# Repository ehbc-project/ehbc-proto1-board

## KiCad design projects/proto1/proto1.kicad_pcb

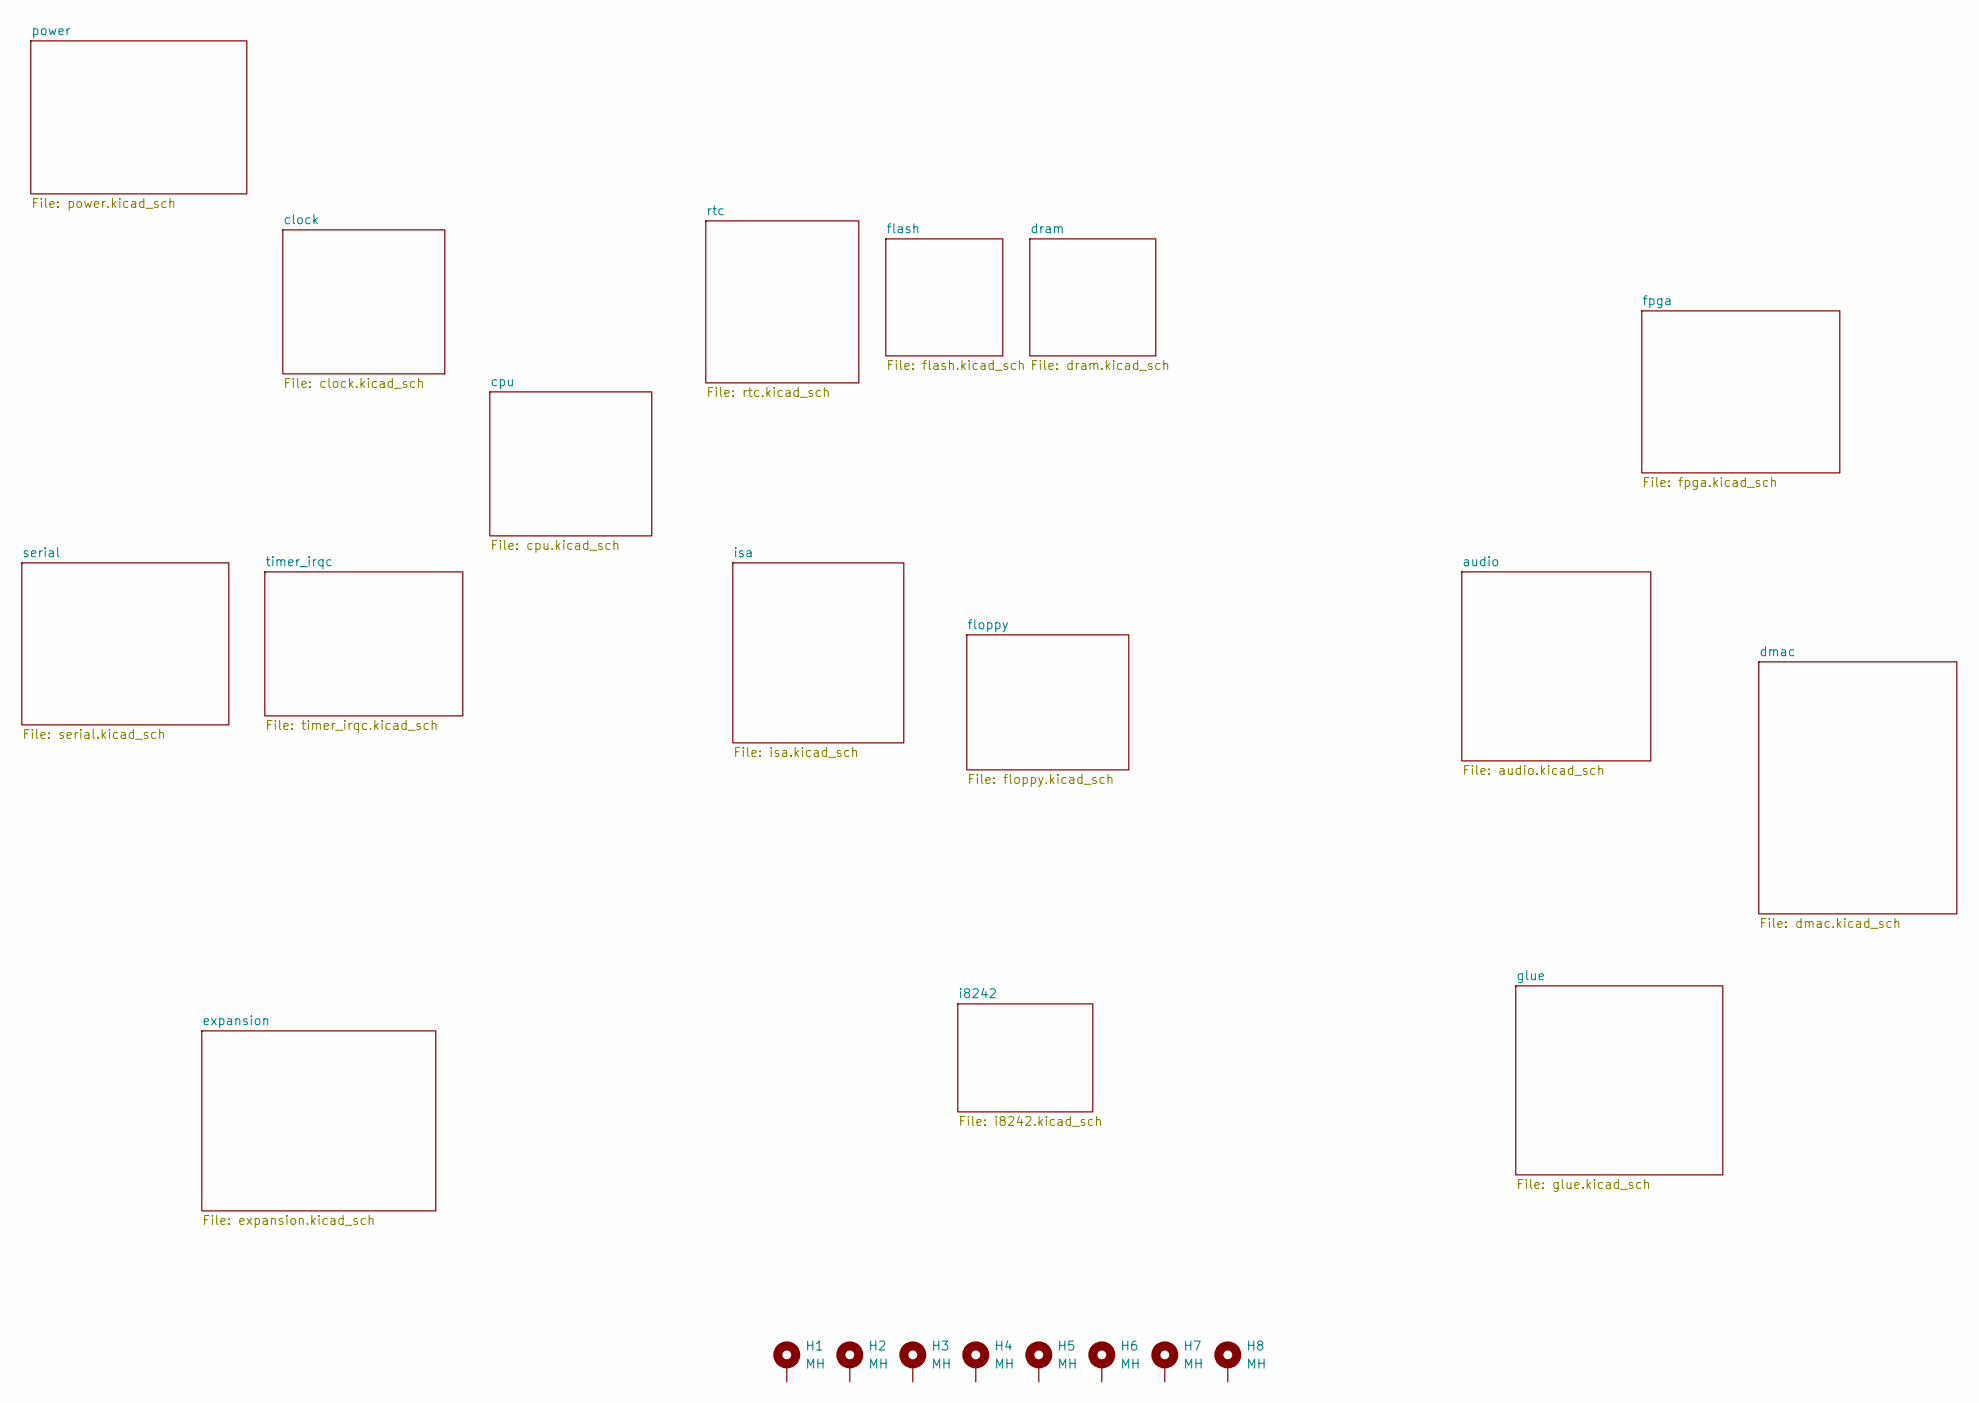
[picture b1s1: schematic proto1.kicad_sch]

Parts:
H1, H2, H3, H4, H5, H6, H7, H8: MH; MountingHole_3.2mm_M3_Pad

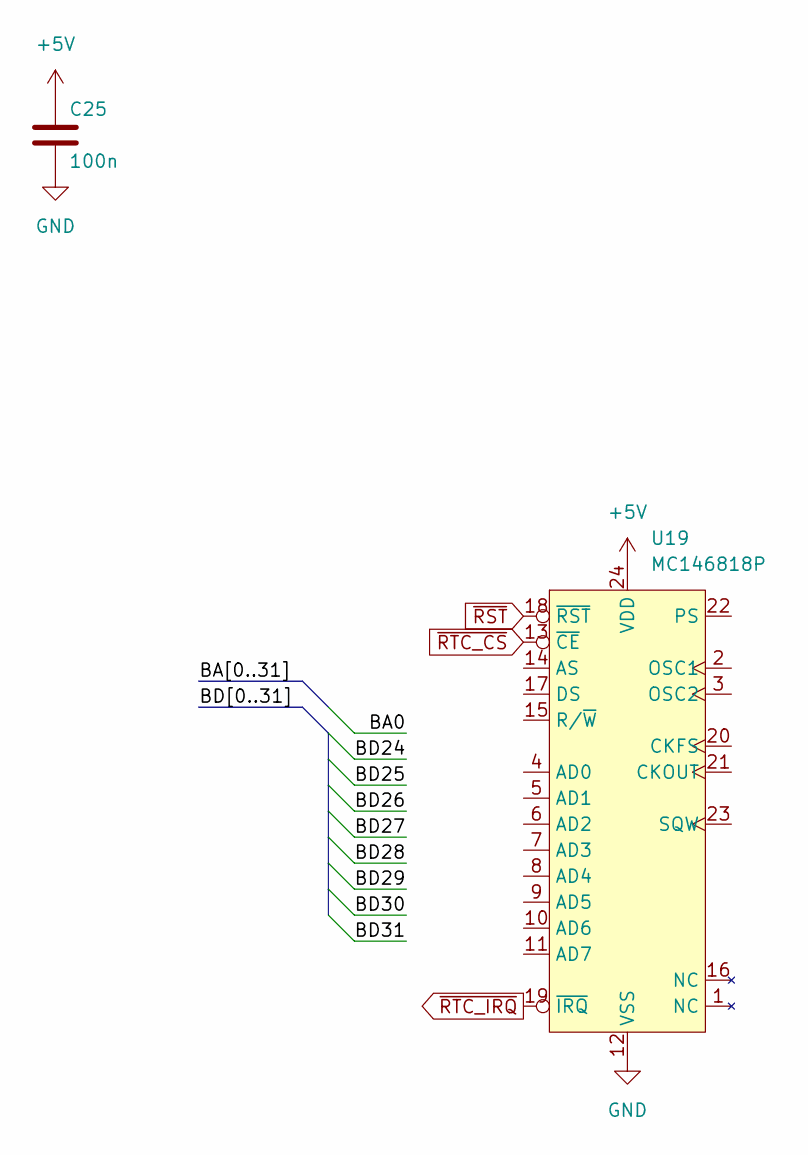
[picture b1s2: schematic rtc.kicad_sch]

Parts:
C25: 100n; C_Disc_D4.3mm_W1.9mm_P5.00mm
U19: MC146818P; DIP-24_W10.16mm

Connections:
+5V: C25.1, U19.24 (VDD); also elsewhere on the board
GND: C25.2, U19.12 (VSS); also elsewhere on the board
~RST: U19.18 (~RST); also elsewhere on the board
~RTC_CS: U19.13 (~CE)
~RTC_IRQ: U19.19 (~IRQ); also elsewhere on the board

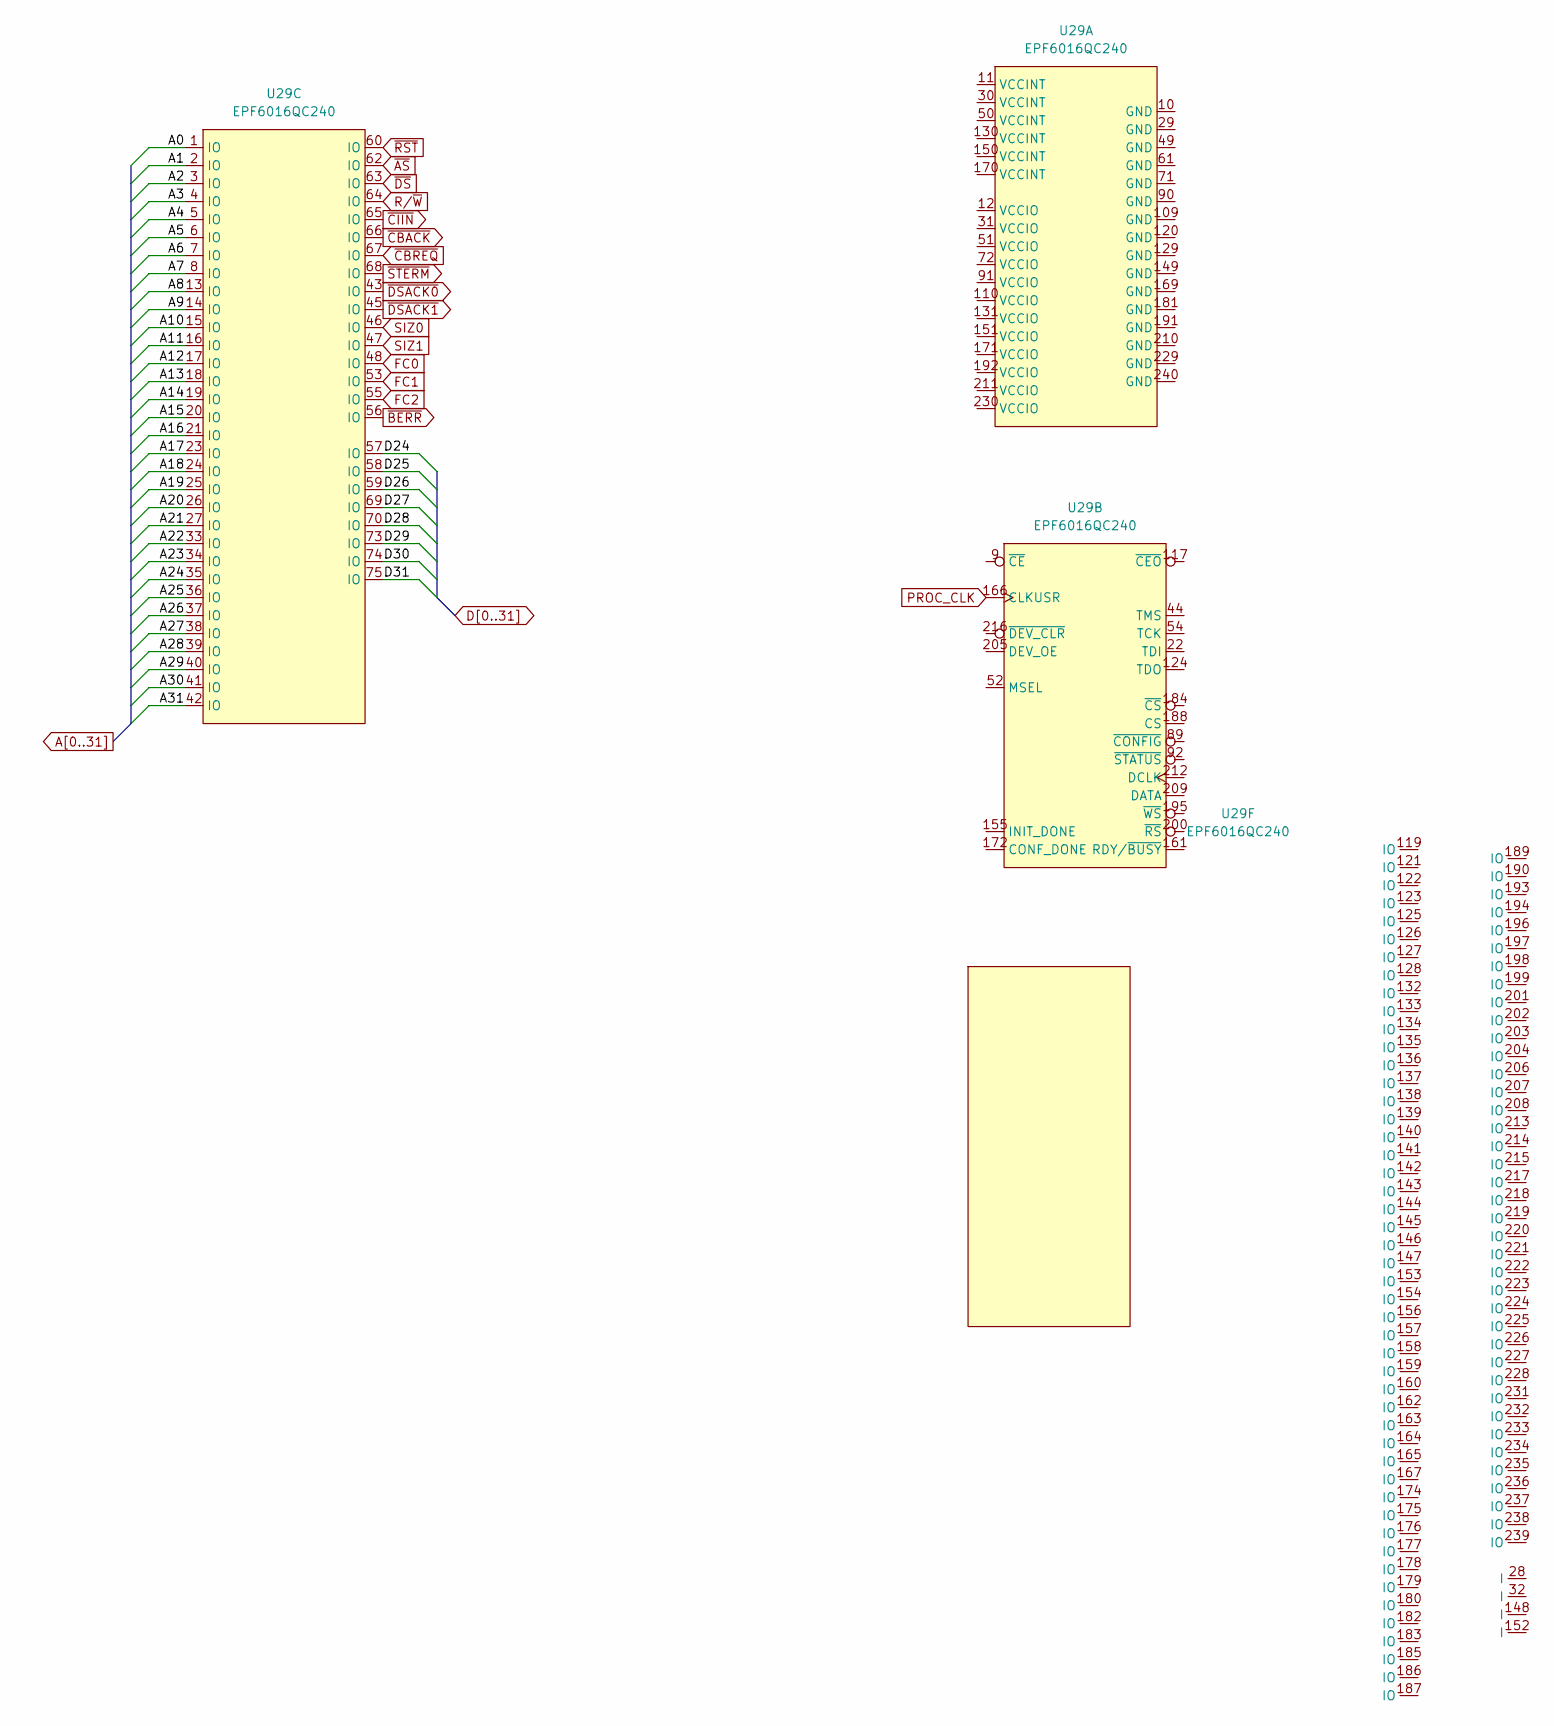
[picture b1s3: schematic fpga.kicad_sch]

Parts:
U29: EPF6016QC240; PQFP-240_32.1x32.1mm_P0.5mm

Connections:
A0: U29.1 (IO); also elsewhere on the board
A1: U29.2 (IO); also elsewhere on the board
A2: U29.3 (IO); also elsewhere on the board
A3: U29.4 (IO); also elsewhere on the board
A4: U29.5 (IO); also elsewhere on the board
A5: U29.6 (IO); also elsewhere on the board
A6: U29.7 (IO); also elsewhere on the board
A7: U29.8 (IO); also elsewhere on the board
A8: U29.13 (IO); also elsewhere on the board
A9: U29.14 (IO); also elsewhere on the board
A10: U29.15 (IO); also elsewhere on the board
A11: U29.16 (IO); also elsewhere on the board
A12: U29.17 (IO); also elsewhere on the board
A13: U29.18 (IO); also elsewhere on the board
A14: U29.19 (IO); also elsewhere on the board
A15: U29.20 (IO); also elsewhere on the board
A16: U29.21 (IO); also elsewhere on the board
A17: U29.23 (IO); also elsewhere on the board
A18: U29.24 (IO); also elsewhere on the board
A19: U29.25 (IO); also elsewhere on the board
A20: U29.26 (IO); also elsewhere on the board
A21: U29.27 (IO); also elsewhere on the board
A22: U29.33 (IO); also elsewhere on the board
A23: U29.34 (IO); also elsewhere on the board
A24: U29.35 (IO); also elsewhere on the board
A25: U29.36 (IO); also elsewhere on the board
A26: U29.37 (IO); also elsewhere on the board
A27: U29.38 (IO); also elsewhere on the board
A28: U29.39 (IO); also elsewhere on the board
A29: U29.40 (IO); also elsewhere on the board
A30: U29.41 (IO); also elsewhere on the board
A31: U29.42 (IO); also elsewhere on the board
D24: U29.57 (IO); also elsewhere on the board
D25: U29.58 (IO); also elsewhere on the board
D26: U29.59 (IO); also elsewhere on the board
D27: U29.69 (IO); also elsewhere on the board
D28: U29.70 (IO); also elsewhere on the board
D29: U29.73 (IO); also elsewhere on the board
D30: U29.74 (IO); also elsewhere on the board
D31: U29.75 (IO); also elsewhere on the board
FC0: U29.48 (IO); also elsewhere on the board
FC1: U29.53 (IO); also elsewhere on the board
FC2: U29.55 (IO); also elsewhere on the board
PROC_CLK: U29.166 (CLKUSR); also elsewhere on the board
R/~W: U29.64 (IO); also elsewhere on the board
SIZ0: U29.46 (IO); also elsewhere on the board
SIZ1: U29.47 (IO); also elsewhere on the board
~AS: U29.62 (IO); also elsewhere on the board
~BERR: U29.56 (IO); also elsewhere on the board
~CBACK: U29.66 (IO); also elsewhere on the board
~CBREQ: U29.67 (IO); also elsewhere on the board
~CIIN: U29.65 (IO); also elsewhere on the board
~DSACK0: U29.43 (IO); also elsewhere on the board
~DSACK1: U29.45 (IO); also elsewhere on the board
~DS: U29.63 (IO); also elsewhere on the board
~RST: U29.60 (IO); also elsewhere on the board
~STERM: U29.68 (IO); also elsewhere on the board

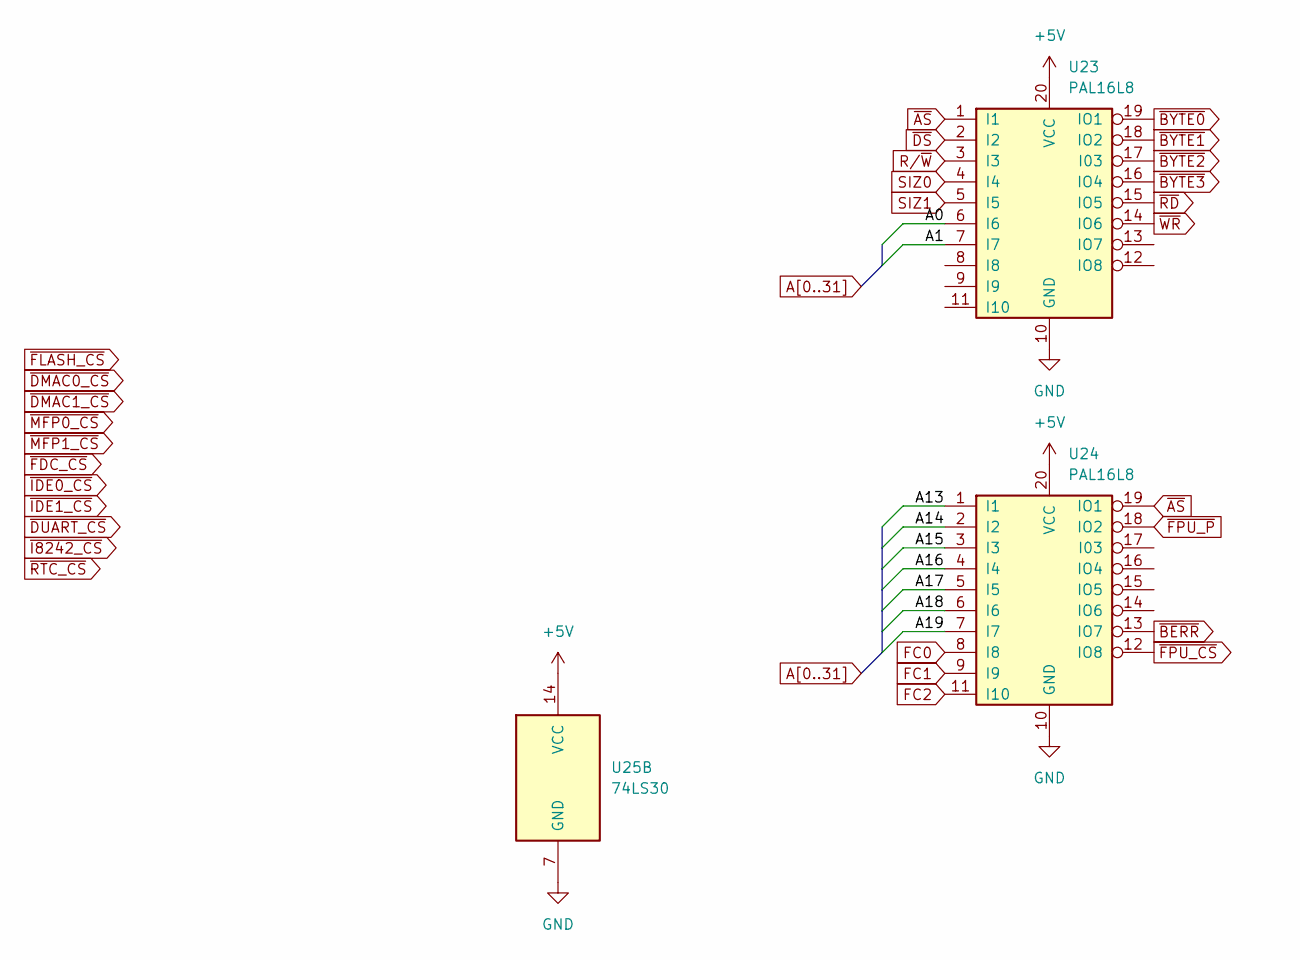
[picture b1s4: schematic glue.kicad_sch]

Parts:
U23, U24: PAL16L8; DIP-20_W7.62mm_Socket
U25: 74LS30

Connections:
+5V: U23.20 (VCC), U24.20 (VCC), U25.14 (VCC); also elsewhere on the board
A0: U23.6 (I6); also elsewhere on the board
A1: U23.7 (I7); also elsewhere on the board
A13: U24.1 (I1); also elsewhere on the board
A14: U24.2 (I2); also elsewhere on the board
A15: U24.3 (I3); also elsewhere on the board
A16: U24.4 (I4); also elsewhere on the board
A17: U24.5 (I5); also elsewhere on the board
A18: U24.6 (I6); also elsewhere on the board
A19: U24.7 (I7); also elsewhere on the board
FC0: U24.8 (I8); also elsewhere on the board
FC1: U24.9 (I9); also elsewhere on the board
FC2: U24.11 (I10); also elsewhere on the board
GND: U23.10 (GND), U24.10 (GND), U25.7 (GND); also elsewhere on the board
R/~W: U23.3 (I3); also elsewhere on the board
SIZ0: U23.4 (I4); also elsewhere on the board
SIZ1: U23.5 (I5); also elsewhere on the board
~AS: U23.1 (I1), U24.19 (IO1); also elsewhere on the board
~BERR: U24.13 (IO7); also elsewhere on the board
~BYTE0: U23.19 (IO1)
~BYTE1: U23.18 (IO2)
~BYTE2: U23.17 (I03)
~BYTE3: U23.16 (IO4)
~DS: U23.2 (I2); also elsewhere on the board
~FPU_CS: U24.12 (IO8); also elsewhere on the board
~FPU_P: U24.18 (IO2); also elsewhere on the board
~RD: U23.15 (IO5); also elsewhere on the board
~WR: U23.14 (IO6); also elsewhere on the board

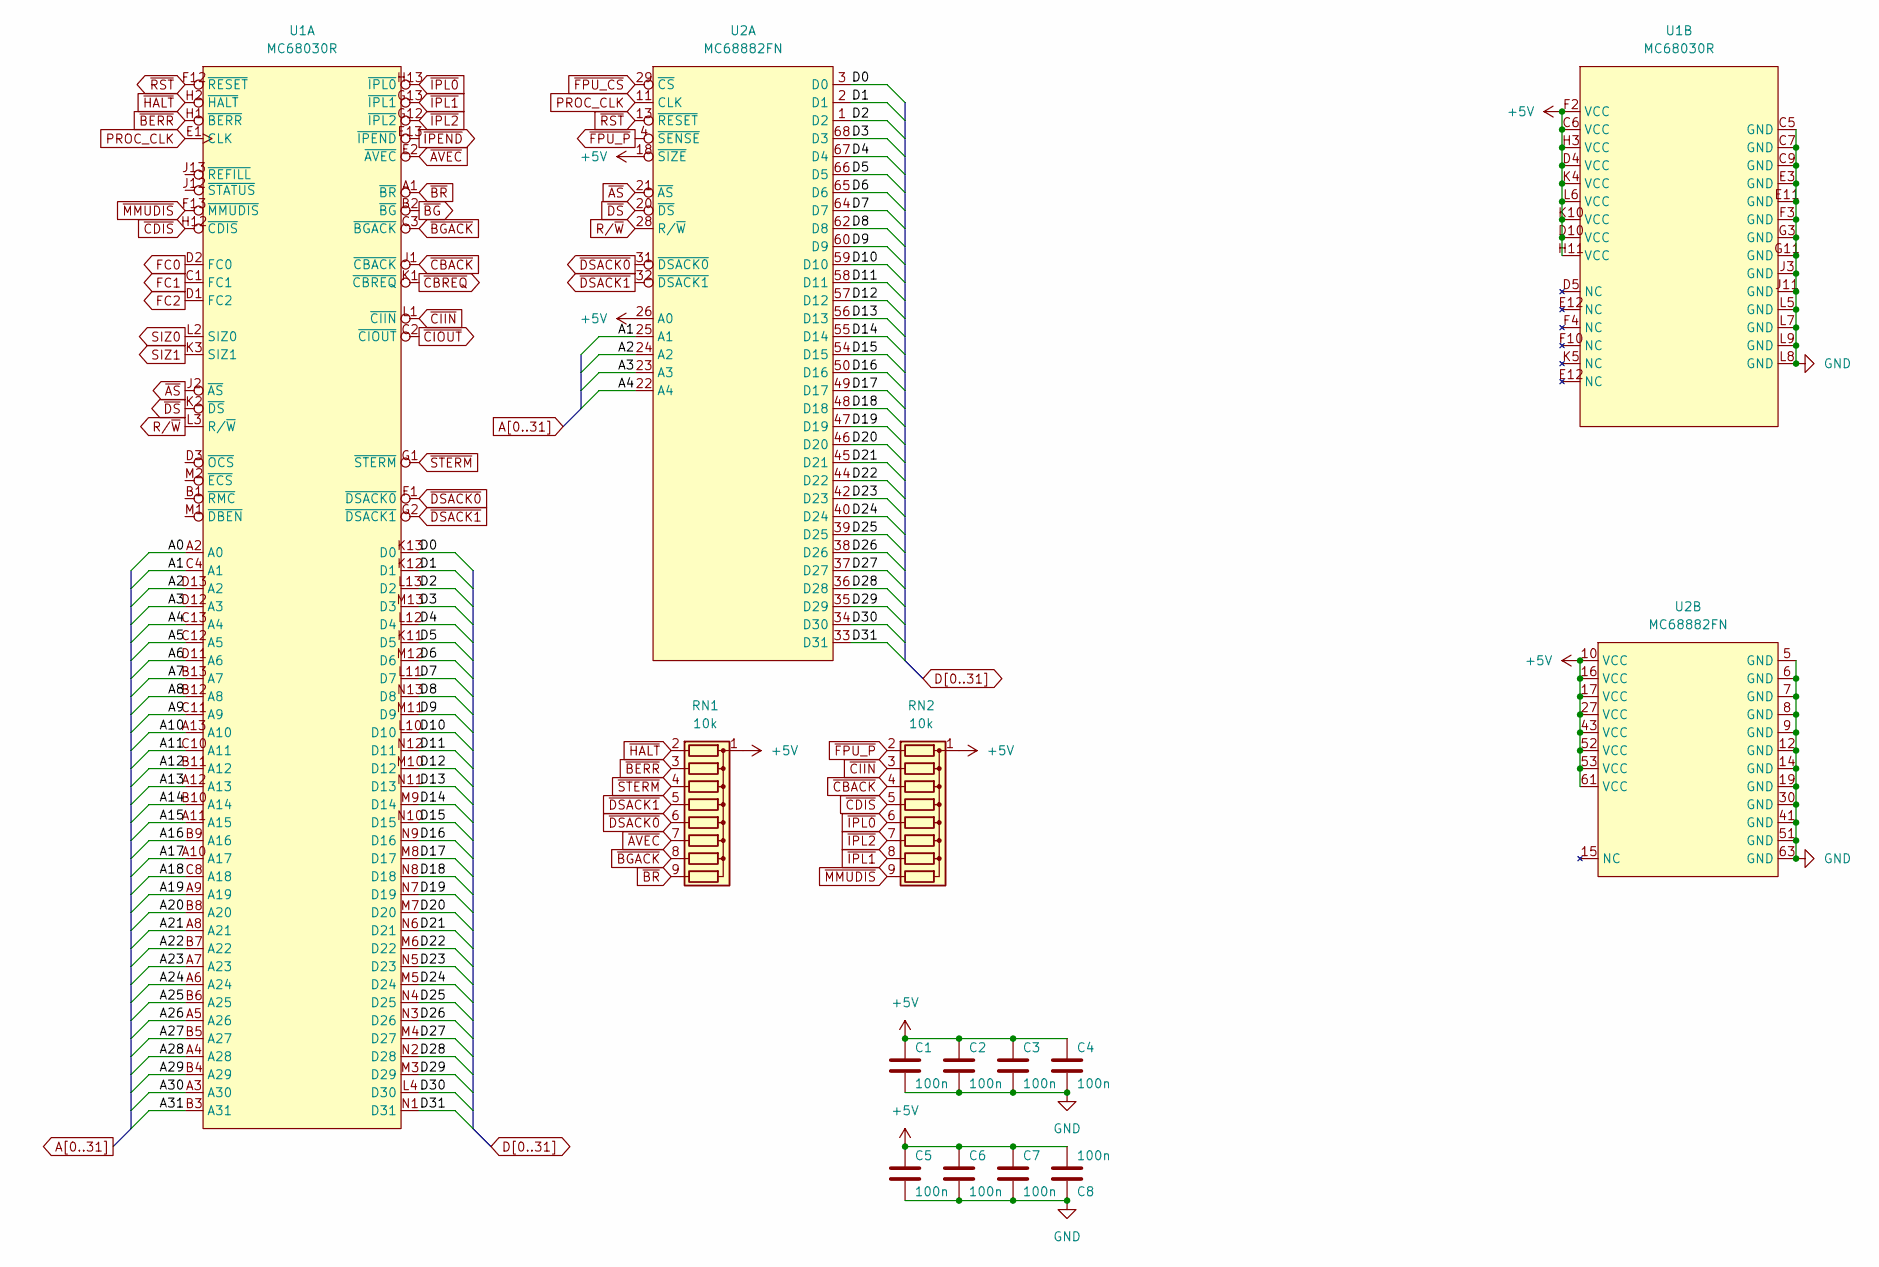
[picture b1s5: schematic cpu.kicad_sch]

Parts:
C1, C2, C3, C4, C5, C6, C7, C8: 100n; C_Disc_D4.3mm_W1.9mm_P5.00mm
RN1, RN2: 10k; R_Array_SIP9
U1: MC68030R; PGA128
U2: MC68882FN; PLCC-68_THT-Socket

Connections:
+5V: C1.1, C2.1, C3.1, C4.1, C5.1, C6.1, C7.1, C8.2, RN1.1 (common), RN2.1 (common), U1.C6 (VCC), U1.D4 (VCC), U1.D10 (VCC), U1.F2 (VCC), U1.H3 (VCC), U1.H11 (VCC), U1.K4 (VCC), U1.K10 (VCC), U1.L6 (VCC), U2.10 (VCC), U2.16 (VCC), U2.17 (VCC), U2.18 (~SIZE), U2.26 (A0), U2.27 (VCC), U2.43 (VCC), U2.52 (VCC), U2.53 (VCC), U2.61 (VCC); also elsewhere on the board
A0: U1.A2 (A0); also elsewhere on the board
A1: U1.C4 (A1), U2.25 (A1); also elsewhere on the board
A2: U1.D13 (A2), U2.24 (A2); also elsewhere on the board
A3: U1.D12 (A3), U2.23 (A3); also elsewhere on the board
A4: U1.C13 (A4), U2.22 (A4); also elsewhere on the board
A5: U1.C12 (A5); also elsewhere on the board
A6: U1.D11 (A6); also elsewhere on the board
A7: U1.B13 (A7); also elsewhere on the board
A8: U1.B12 (A8); also elsewhere on the board
A9: U1.C11 (A9); also elsewhere on the board
A10: U1.A13 (A10); also elsewhere on the board
A11: U1.C10 (A11); also elsewhere on the board
A12: U1.B11 (A12); also elsewhere on the board
A13: U1.A12 (A13); also elsewhere on the board
A14: U1.B10 (A14); also elsewhere on the board
A15: U1.A11 (A15); also elsewhere on the board
A16: U1.B9 (A16); also elsewhere on the board
A17: U1.A10 (A17); also elsewhere on the board
A18: U1.C8 (A18); also elsewhere on the board
A19: U1.A9 (A19); also elsewhere on the board
A20: U1.B8 (A20); also elsewhere on the board
A21: U1.A8 (A21); also elsewhere on the board
A22: U1.B7 (A22); also elsewhere on the board
A23: U1.A7 (A23); also elsewhere on the board
A24: U1.A6 (A24); also elsewhere on the board
A25: U1.B6 (A25); also elsewhere on the board
A26: U1.A5 (A26); also elsewhere on the board
A27: U1.B5 (A27); also elsewhere on the board
A28: U1.A4 (A28); also elsewhere on the board
A29: U1.B4 (A29); also elsewhere on the board
A30: U1.A3 (A30); also elsewhere on the board
A31: U1.B3 (A31); also elsewhere on the board
D0: U1.K13 (D0), U2.3 (D0); also elsewhere on the board
D1: U1.K12 (D1), U2.2 (D1); also elsewhere on the board
D2: U1.L13 (D2), U2.1 (D2); also elsewhere on the board
D3: U1.M13 (D3), U2.68 (D3); also elsewhere on the board
D4: U1.L12 (D4), U2.67 (D4); also elsewhere on the board
D5: U1.K11 (D5), U2.66 (D5); also elsewhere on the board
D6: U1.M12 (D6), U2.65 (D6); also elsewhere on the board
D7: U1.L11 (D7), U2.64 (D7); also elsewhere on the board
D8: U1.N13 (D8), U2.62 (D8); also elsewhere on the board
D9: U1.M11 (D9), U2.60 (D9); also elsewhere on the board
D10: U1.L10 (D10), U2.59 (D10); also elsewhere on the board
D11: U1.N12 (D11), U2.58 (D11); also elsewhere on the board
D12: U1.M10 (D12), U2.57 (D12); also elsewhere on the board
D13: U1.N11 (D13), U2.56 (D13); also elsewhere on the board
D14: U1.M9 (D14), U2.55 (D14); also elsewhere on the board
D15: U1.N10 (D15), U2.54 (D15); also elsewhere on the board
D16: U1.N9 (D16), U2.50 (D16); also elsewhere on the board
D17: U1.M8 (D17), U2.49 (D17); also elsewhere on the board
D18: U1.N8 (D18), U2.48 (D18); also elsewhere on the board
D19: U1.N7 (D19), U2.47 (D19); also elsewhere on the board
D20: U1.M7 (D20), U2.46 (D20); also elsewhere on the board
D21: U1.N6 (D21), U2.45 (D21); also elsewhere on the board
D22: U1.M6 (D22), U2.44 (D22); also elsewhere on the board
D23: U1.N5 (D23), U2.42 (D23); also elsewhere on the board
D24: U1.M5 (D24), U2.40 (D24); also elsewhere on the board
D25: U1.N4 (D25), U2.39 (D25); also elsewhere on the board
D26: U1.N3 (D26), U2.38 (D26); also elsewhere on the board
D27: U1.M4 (D27), U2.37 (D27); also elsewhere on the board
D28: U1.N2 (D28), U2.36 (D28); also elsewhere on the board
D29: U1.M3 (D29), U2.35 (D29); also elsewhere on the board
D30: U1.L4 (D30), U2.34 (D30); also elsewhere on the board
D31: U1.N1 (D31), U2.33 (D31); also elsewhere on the board
FC0: U1.D2 (FC0); also elsewhere on the board
FC1: U1.C1 (FC1); also elsewhere on the board
FC2: U1.D1 (FC2); also elsewhere on the board
GND: C1.2, C2.2, C3.2, C4.2, C5.2, C6.2, C7.2, C8.1, U1.C5 (GND), U1.C7 (GND), U1.C9 (GND), U1.E3 (GND), U1.E11 (GND), U1.F3 (GND), U1.G3 (GND), U1.G11 (GND), U1.J3 (GND), U1.J11 (GND), U1.L5 (GND), U1.L7 (GND), U1.L8 (GND), U1.L9 (GND), U2.5 (GND), U2.6 (GND), U2.7 (GND), U2.8 (GND), U2.9 (GND), U2.12 (GND), U2.14 (GND), U2.19 (GND), U2.30 (GND), U2.41 (GND), U2.51 (GND), U2.63 (GND); also elsewhere on the board
PROC_CLK: U1.E1 (CLK), U2.11 (CLK); also elsewhere on the board
R/~W: U1.L3 (R/~W), U2.28 (R/~W); also elsewhere on the board
SIZ0: U1.L2 (SIZ0); also elsewhere on the board
SIZ1: U1.K3 (SIZ1); also elsewhere on the board
~AS: U1.J2 (~AS), U2.21 (~AS); also elsewhere on the board
~AVEC: RN1.7 (R6), U1.E2 (~AVEC)
~BERR: RN1.3 (R2), U1.H1 (~BERR); also elsewhere on the board
~BGACK: RN1.8 (R7), U1.C3 (~BGACK); also elsewhere on the board
~BG: U1.B2 (~BG); also elsewhere on the board
~BR: RN1.9 (R8), U1.A1 (~BR); also elsewhere on the board
~CBACK: RN2.4 (R3), U1.J1 (~CBACK); also elsewhere on the board
~CBREQ: U1.K1 (~CBREQ); also elsewhere on the board
~CDIS: RN2.5 (R4), U1.H12 (~CDIS)
~CIIN: RN2.3 (R2), U1.L1 (~CIIN); also elsewhere on the board
~CIOUT: U1.C2 (~CIOUT)
~DSACK0: RN1.6 (R5), U1.F1 (~DSACK0), U2.31 (~DSACK0); also elsewhere on the board
~DSACK1: RN1.5 (R4), U1.G2 (~DSACK1), U2.32 (~DSACK1); also elsewhere on the board
~DS: U1.K2 (~DS), U2.20 (~DS); also elsewhere on the board
~FPU_CS: U2.29 (~CS); also elsewhere on the board
~FPU_P: RN2.2 (R1), U2.4 (~SENSE); also elsewhere on the board
~HALT: RN1.2 (R1), U1.H2 (~HALT); also elsewhere on the board
~IPEND: U1.E13 (~IPEND)
~IPL0: RN2.6 (R5), U1.H13 (~IPL0); also elsewhere on the board
~IPL1: RN2.8 (R7), U1.G13 (~IPL1); also elsewhere on the board
~IPL2: RN2.7 (R6), U1.G12 (~IPL2); also elsewhere on the board
~MMUDIS: RN2.9 (R8), U1.F13 (~MMUDIS)
~RST: U1.F12 (~RESET), U2.13 (~RESET); also elsewhere on the board
~STERM: RN1.4 (R3), U1.G1 (~STERM); also elsewhere on the board

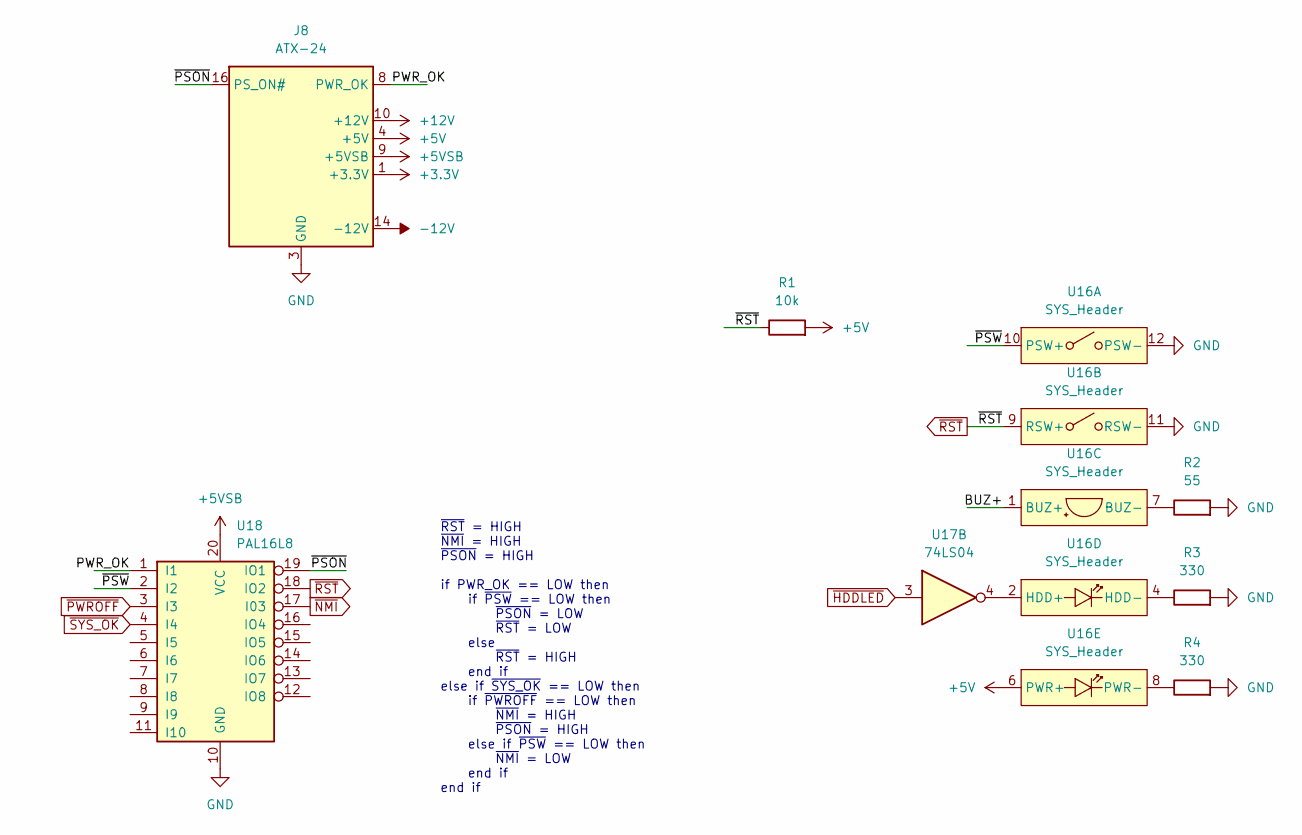
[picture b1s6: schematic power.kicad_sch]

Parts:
J8: ATX-24; Molex_Mini-Fit_Jr_5566-24A_2x12_P4.20mm_Vertical
R1: 10k; R_Axial_DIN0204_L3.6mm_D1.6mm_P7.62mm_Horizontal
R2: 55; R_Axial_DIN0204_L3.6mm_D1.6mm_P7.62mm_Horizontal
R3, R4: 330; R_Axial_DIN0204_L3.6mm_D1.6mm_P7.62mm_Horizontal
U16: SYS_Header; PinHeader_2x06_P2.54mm_Vertical
U17: 74LS04; DIP-14_W7.62mm_Socket
U18: PAL16L8

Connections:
+3.3V: J8.1 (+3.3V), J8.2 (+3.3V), J8.12 (+3.3V), J8.13 (+3.3V)
+5V: J8.4 (+5V), J8.6 (+5V), J8.21 (+5V), J8.22 (+5V), J8.23 (+5V), R1.2, U16.6 (PWR+); also elsewhere on the board
+5VSB: J8.9 (+5VSB), U18.20 (VCC)
+12V: J8.10 (+12V), J8.11 (+12V); also elsewhere on the board
-12V: J8.14 (-12V); also elsewhere on the board
/power/BUZ+: U16.1 (BUZ+)
/power/PWR_OK: J8.8 (PWR_OK), U18.1 (I1)
/power/~PSON: J8.16 (PS_ON#), U18.19 (IO1)
/power/~PSW: U16.10 (PSW+), U18.2 (I2)
GND: J8.3 (GND), J8.5 (GND), J8.7 (GND), J8.15 (GND), J8.17 (GND), J8.18 (GND), J8.19 (GND), J8.24 (GND), R2.2, R3.2, R4.2, U16.11 (RSW-), U16.12 (PSW-), U18.10 (GND); also elsewhere on the board
unnamed: R2.1, U16.7 (BUZ-)
unnamed: U16.2 (HDD+), U17.4
unnamed: R3.1, U16.4 (HDD-)
unnamed: R4.1, U16.8 (PWR-)
~HDDLED: U17.3; also elsewhere on the board
~RST: R1.1, U16.9 (RSW+), U18.18 (IO2); also elsewhere on the board

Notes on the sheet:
~{RST} = HIGH ~{NMI} = HIGH ~{PSON} = HIGH if PWR_OK == LOW then if ~{PSW} == LOW then ~{PSON} = LOW ~{RST} = LOW else ~{RST} = HIGH end if else if ~{SYS_OK} == LOW then if ~{PWROFF} == LOW then ~{NMI} = HIGH ~{PSON} = HIGH else if ~{PSW} == LOW then ~{NMI} = LOW end if end if

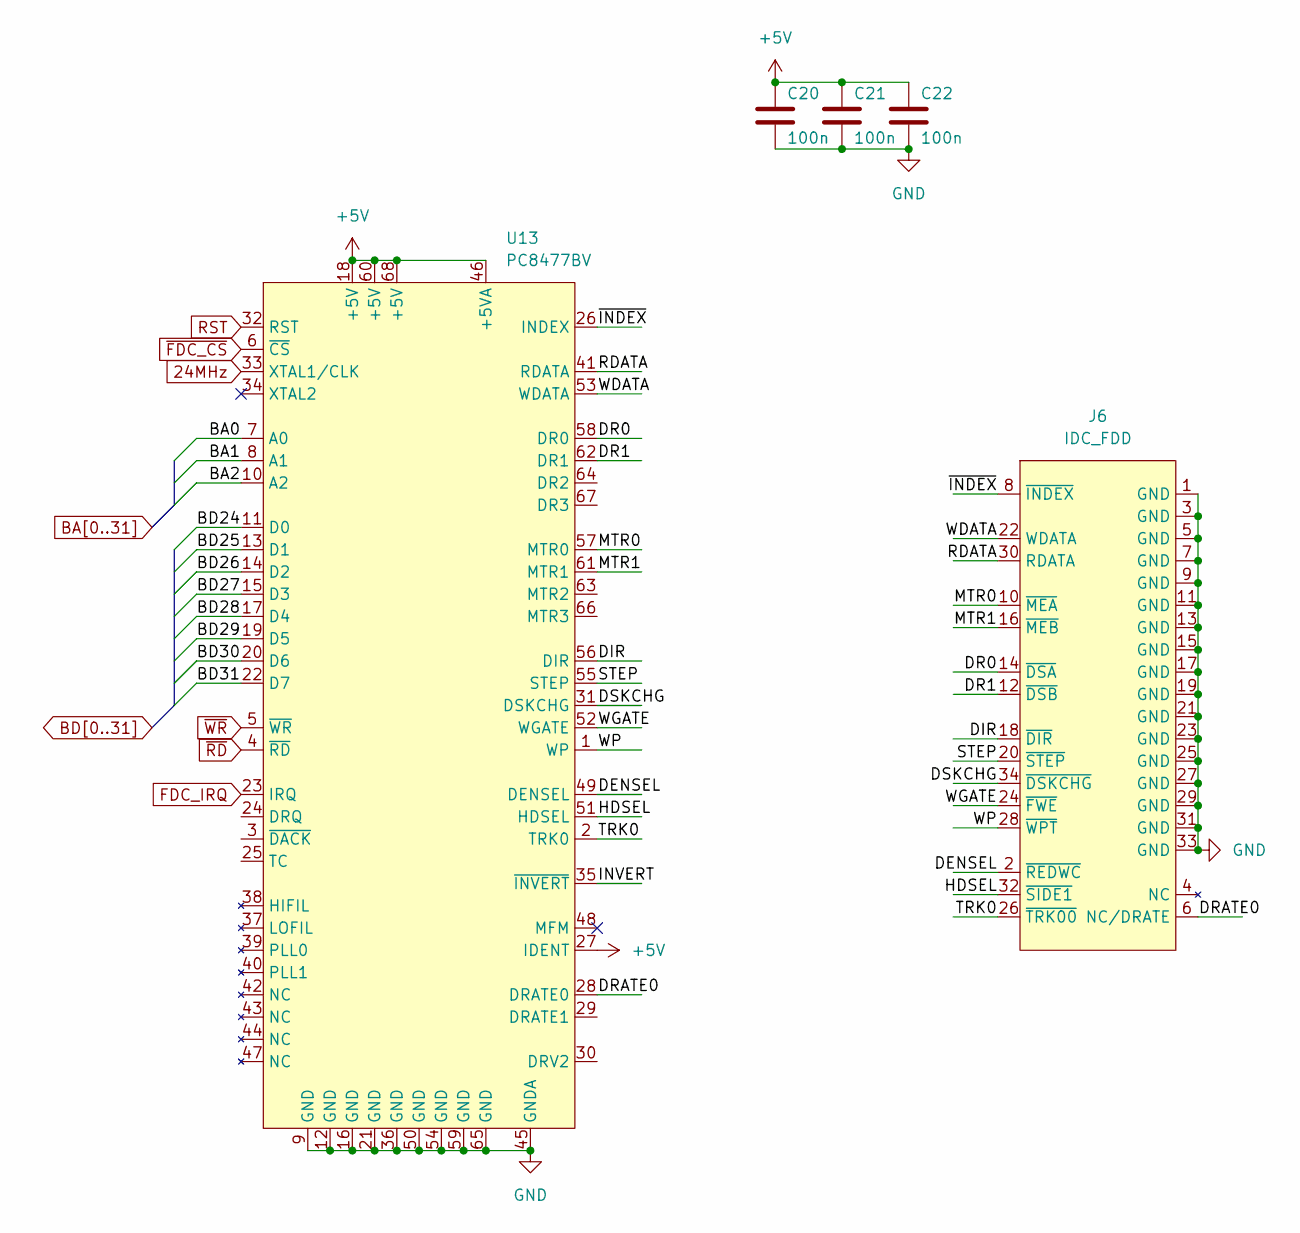
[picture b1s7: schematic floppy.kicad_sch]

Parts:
C20, C21, C22: 100n; C_Disc_D4.3mm_W1.9mm_P5.00mm
J6: IDC_FDD; IDC-Header_2x17_P2.54mm_Vertical
U13: PC8477BV; PLCC-68_THT-Socket

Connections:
24MHz: U13.33 (XTAL1/CLK); also elsewhere on the board
+5V: C20.1, C21.1, C22.1, U13.18 (+5V), U13.27 (IDENT), U13.46 (+5VA), U13.60 (+5V), U13.68 (+5V); also elsewhere on the board
/floppy/DENSEL: J6.2 (~REDWC), U13.49 (DENSEL)
/floppy/DIR: J6.18 (~DIR), U13.56 (DIR)
/floppy/DR0: J6.14 (~DSA), U13.58 (DR0)
/floppy/DR1: J6.12 (~DSB), U13.62 (DR1)
/floppy/DRATE0: J6.6 (NC/DRATE), U13.28 (DRATE0)
/floppy/DSKCHG: J6.34 (~DSKCHG), U13.31 (DSKCHG)
/floppy/HDSEL: J6.32 (~SIDE1), U13.51 (HDSEL)
/floppy/INVERT: U13.35 (~INVERT)
/floppy/MTR0: J6.10 (~MEA), U13.57 (MTR0)
/floppy/MTR1: J6.16 (~MEB), U13.61 (MTR1)
/floppy/RDATA: J6.30 (RDATA), U13.41 (RDATA)
/floppy/STEP: J6.20 (~STEP), U13.55 (STEP)
/floppy/TRK0: J6.26 (~TRK00), U13.2 (TRK0)
/floppy/WDATA: J6.22 (WDATA), U13.53 (WDATA)
/floppy/WGATE: J6.24 (~FWE), U13.52 (WGATE)
/floppy/WP: J6.28 (~WPT), U13.1 (WP)
/floppy/~INDEX: J6.8 (~INDEX), U13.26 (INDEX)
BA0: U13.7 (A0); also elsewhere on the board
BA1: U13.8 (A1); also elsewhere on the board
BA2: U13.10 (A2); also elsewhere on the board
BD24: U13.11 (D0); also elsewhere on the board
BD25: U13.13 (D1); also elsewhere on the board
BD26: U13.14 (D2); also elsewhere on the board
BD27: U13.15 (D3); also elsewhere on the board
BD28: U13.17 (D4); also elsewhere on the board
BD29: U13.19 (D5); also elsewhere on the board
BD30: U13.20 (D6); also elsewhere on the board
BD31: U13.22 (D7); also elsewhere on the board
GND: C20.2, C21.2, C22.2, J6.1 (GND), J6.3 (GND), J6.5 (GND), J6.7 (GND), J6.9 (GND), J6.11 (GND), J6.13 (GND), J6.15 (GND), J6.17 (GND), J6.19 (GND), J6.21 (GND), J6.23 (GND), J6.25 (GND), J6.27 (GND), J6.29 (GND), J6.31 (GND), J6.33 (GND), U13.9 (GND), U13.12 (GND), U13.16 (GND), U13.21 (GND), U13.36 (GND), U13.45 (GNDA), U13.50 (GND), U13.54 (GND), U13.59 (GND), U13.65 (GND); also elsewhere on the board
RST: U13.32 (RST); also elsewhere on the board
~FDC_CS: U13.6 (~CS)
~RD: U13.4 (~RD); also elsewhere on the board
~WR: U13.5 (~WR); also elsewhere on the board
